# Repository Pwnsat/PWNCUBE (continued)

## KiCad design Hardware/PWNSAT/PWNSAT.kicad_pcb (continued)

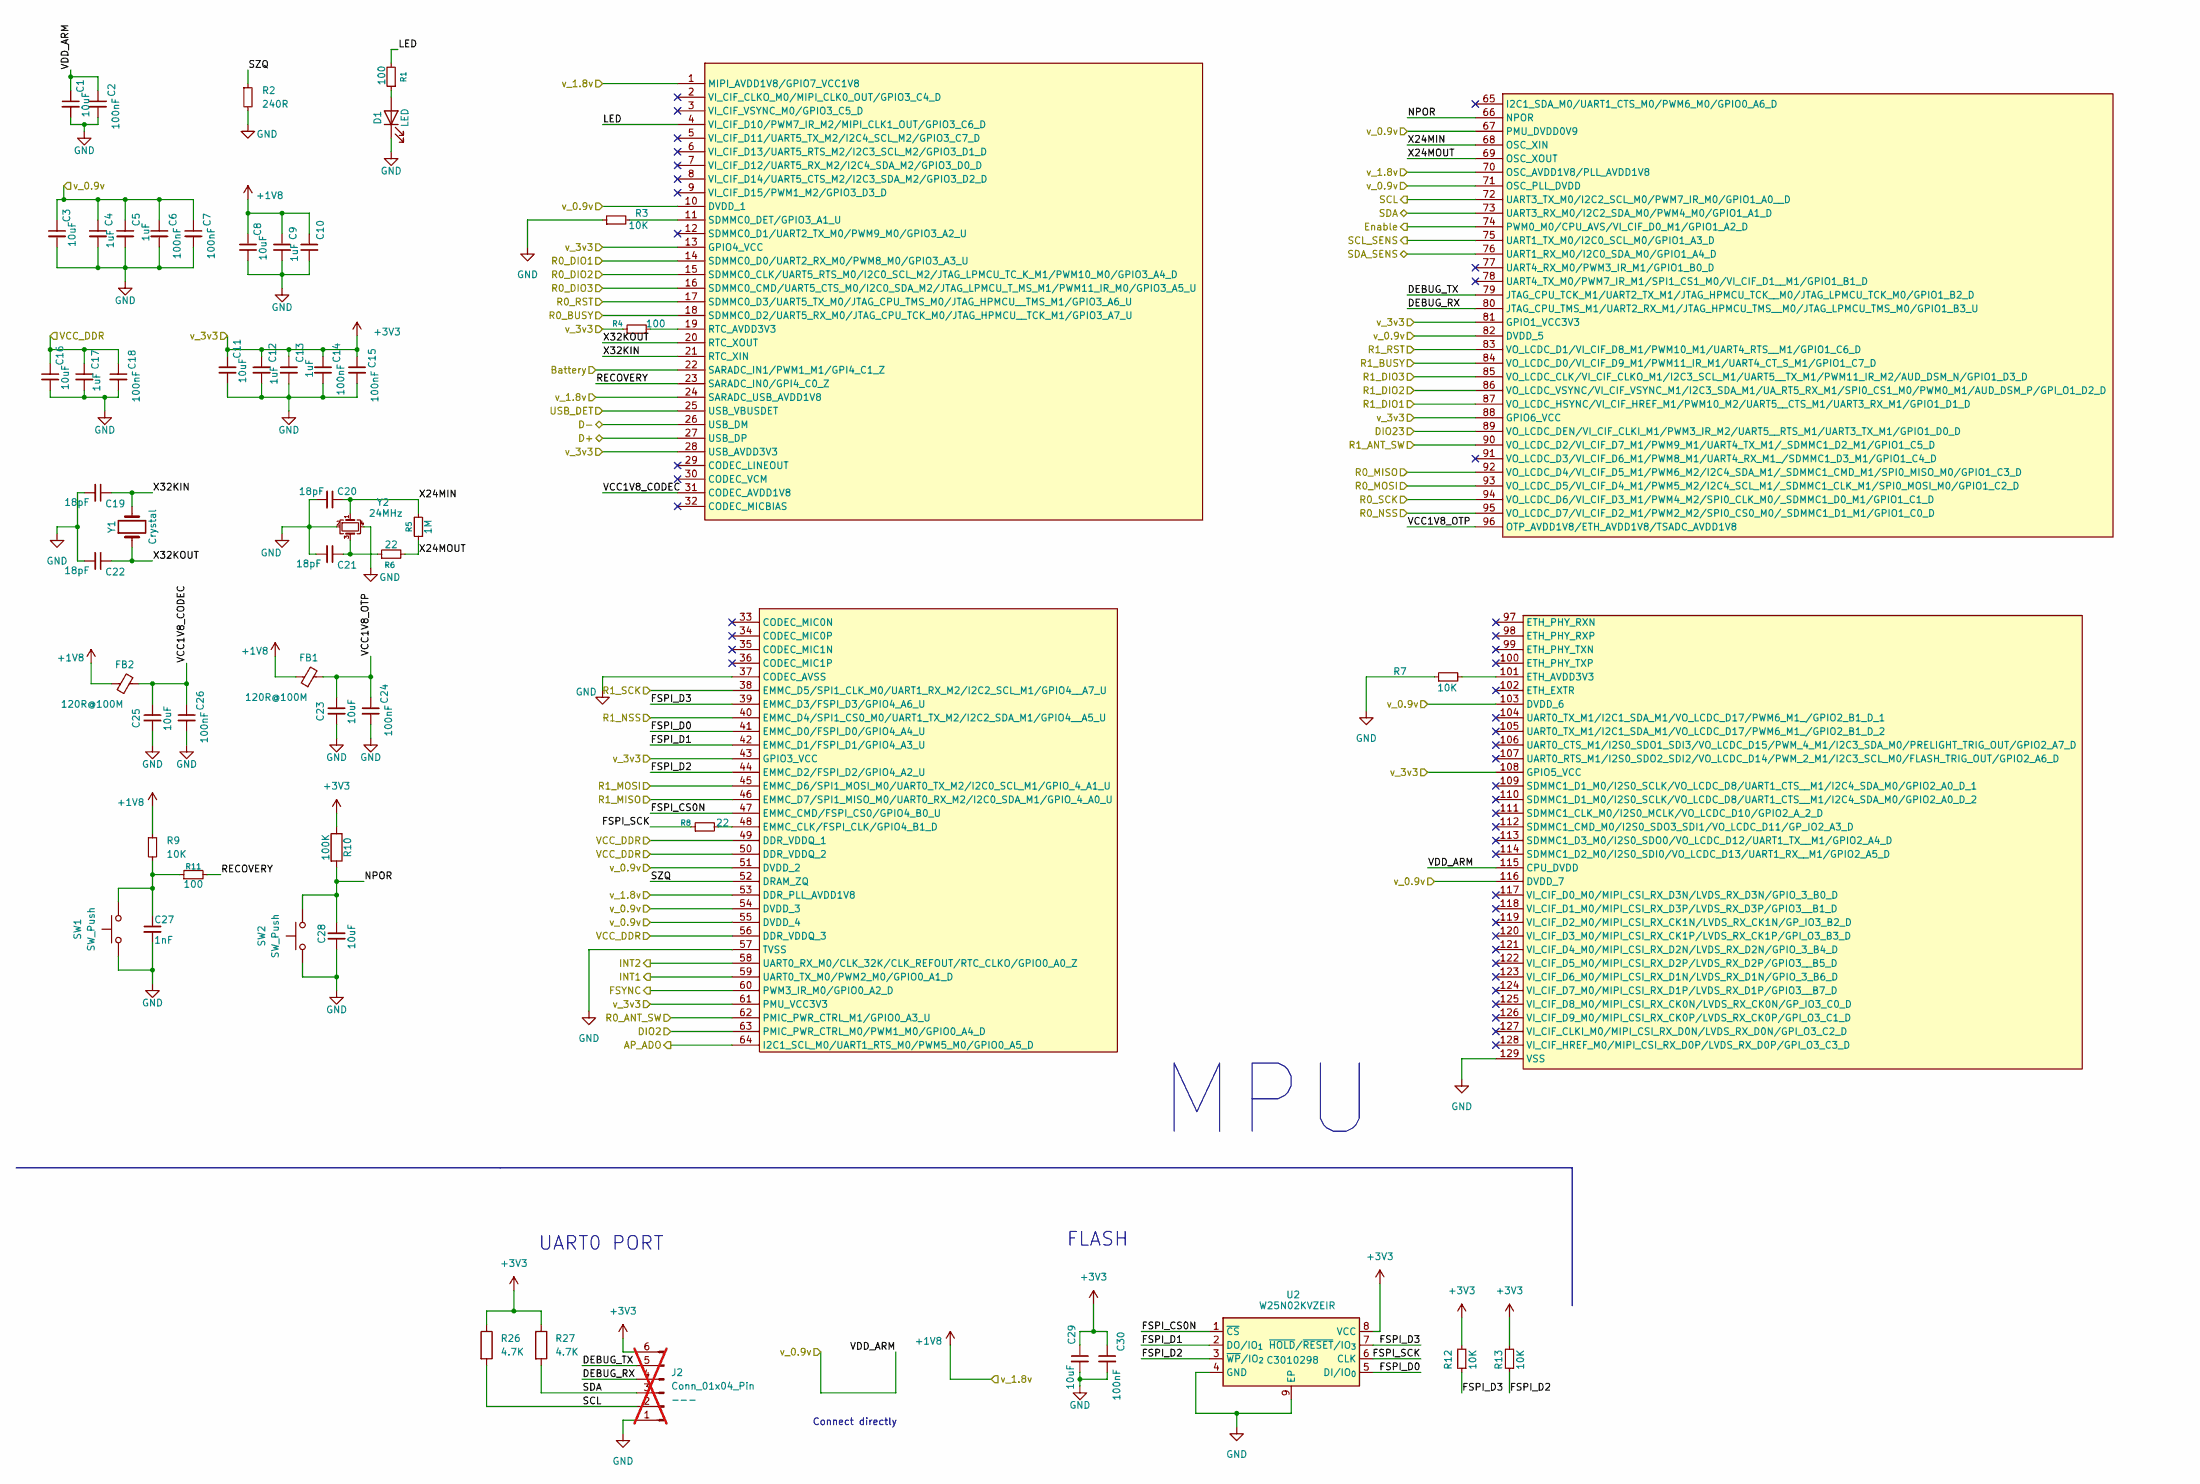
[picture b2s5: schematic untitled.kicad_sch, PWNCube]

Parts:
C1, C3, C8, C11, C16, C23, C25, C28, C29: 10uF; C_0603_1608Metric; LCSC# C96446
C2, C6, C7, C14, C15, C18, C24, C26, C30: 100nF; C_0402_1005Metric_Pad0.74x0.62mm_HandSolder; LCSC# C56392
C4, C5, C9, C10, C12, C13, C17: 1uF; C_0402_1005Metric_Pad0.74x0.62mm_HandSolder; LCSC# C52923
C19, C20, C21, C22: 18pF; C_0402_1005Metric_Pad0.74x0.62mm_HandSolder; LCSC# C161534
C27: 1nF; C_0402_1005Metric_Pad0.74x0.62mm_HandSolder; LCSC# C189467
D1: LED; LED_0603_1608Metric; LCSC# C375573
FB1, FB2: 120R@100M; L_0603_1608Metric; LCSC# C14709
J2: Conn_01x04_Pin; PinHeader_1x06_P2.54mm_Vertical; LCSC# ---; not fitted
R1, R4, R11: 100; R_0603_1608Metric; LCSC# C253328
R2: 240R; R_0402_1005Metric_Pad0.72x0.64mm_HandSolder; LCSC# C728568
R3, R7, R9, R12, R13: 10K; R_0402_1005Metric_Pad0.72x0.64mm_HandSolder; LCSC# C2759535
R5: 1M; R_0402_1005Metric_Pad0.72x0.64mm_HandSolder; LCSC# C131492
R6, R8: 22; R_0603_1608Metric; LCSC# C313374
R10: 100K; R_0402_1005Metric_Pad0.72x0.64mm_HandSolder; LCSC# C844674
R26, R27: 4.7K; R_0402_1005Metric_Pad0.72x0.64mm_HandSolder; LCSC# C400631
SW1, SW2: SW_Push; TS1088R02026; LCSC# C455281
U1: RV1106G3; LCSC# C5328706
U2: W25N02KVZEIR; WSON-8-1EP_8x6mm_P1.27mm_EP3.4x4.3mm; LCSC# C3010298
Y1: Crystal; Crystal_SMD_3215-2Pin_3.2x1.5mm; LCSC# C620155
Y2: 24MHz; Crystal_SMD_3225-4Pin_3.2x2.5mm; LCSC# C70590

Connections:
+1V8: C8.1, C9.1, C10.1, FB1.1, FB2.1, R9.1, U1.1 (MIPI_AVDD1V8/GPIO7_VCC1V8), U1.24 (SARADC_USB_AVDD1V8), U1.53 (DDR_PLL_AVDD1V8), U1.70 (OSC_AVDD1V8/PLL_AVDD1V8); also elsewhere on the board
+3V3: C11.1, C12.1, C13.1, C14.1, C15.1, C29.1, C30.1, J2.6, R4.1, R10.1, R12.2, R13.2, R26.1, R27.1, U1.13 (GPIO4_VCC), U1.28 (USB_AVDD3V3), U1.43 (GPIO3_VCC), U1.61 (PMU_VCC3V3), U1.81 (GPIO1_VCC3V3), U1.88 (GPIO6_VCC), U1.108 (GPIO5_VCC), U2.8 (VCC); also elsewhere on the board
/Sensor/AP_ADO: U1.64 (I2C1_SCL_M0/UART1_RTS_M0/PWM5_M0/GPIO0_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); also elsewhere on the board
/Sensor/DIO2: U1.63 (PMIC_PWR_CTRL_M0/PWM1_M0/GPIO0_A4_D); also elsewhere on the board
/Sensor/DIO23: U1.89 (VO_LCDC_DEN/VI_CIF_CLKI_M1/PWM3_IR_M2/U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); also elsewhere on the board
/Sensor/FSYNC: U1.60 (PWM3_IR_M0/GPIO0_A2_D); also elsewhere on the board
/Sensor/INT1: U1.59 (UART0_TX_M0/PWM2_M0/GPIO0_A1_D); also elsewhere on the board
/Sensor/INT2: U1.58 (UART0_RX_M0/CLK_32K/CLK_REFOUT/RTC_CLKO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); also elsewhere on the board
/Sensor/R0_ANT_SW: U1.62 (PMIC_PWR_CTRL_M1/GPIO0_A3_U); also elsewhere on the board
/Sensor/R0_BUSY: U1.18 (SDMMC0_D2/UART5_RX_M0/JTAG_CPU_TCK_M0/J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); also elsewhere on the board
/Sensor/R0_DIO1: U1.14 (SDMMC0_D0/UART2_RX_M0/PWM8_M0/GPIO3_A3_U); also elsewhere on the board
/Sensor/R0_DIO2: U1.15 (SDMMC0_CLK/UART5_RTS_M0/I2C0_SCL_M2/JTA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); also elsewhere on the board
/Sensor/R0_DIO3: U1.16 (SDMMC0_CMD/UART5_CTS_M0/I2C0_SDA_M2/JTA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); also elsewhere on the board
/Sensor/R0_MISO: U1.92 (VO_LCDC_D4/VI_CIF_D5_M1/PWM6_M2/I2C4_SD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); also elsewhere on the board
/Sensor/R0_MOSI: U1.93 (VO_LCDC_D5/VI_CIF_D4_M1/PWM5_M2/I2C4_SC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); also elsewhere on the board
/Sensor/R0_NSS: U1.95 (VO_LCDC_D7/VI_CIF_D2_M1/PWM2_M2/SPI0_CS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); also elsewhere on the board
/Sensor/R0_RST: U1.17 (SDMMC0_D3/UART5_TX_M0/JTAG_CPU_TMS_M0/J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); also elsewhere on the board
/Sensor/R0_SCK: U1.94 (VO_LCDC_D6/VI_CIF_D3_M1/PWM4_M2/SPI0_CL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); also elsewhere on the board
/Sensor/R1_ANT_SW: U1.90 (VO_LCDC_D2/VI_CIF_D7_M1/PWM9_M1/UART4_T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); also elsewhere on the board
/Sensor/R1_BUSY: U1.84 (VO_LCDC_D0/VI_CIF_D9_M1/PWM11_IR_M1/UAR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); also elsewhere on the board
/Sensor/R1_DIO1: U1.87 (VO_LCDC_HSYNC/VI_CIF_HREF_M1/PWM10_M2/U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); also elsewhere on the board
/Sensor/R1_DIO2: U1.86 (VO_LCDC_VSYNC/VI_CIF_VSYNC_M1/I2C3_SDA_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); also elsewhere on the board
/Sensor/R1_DIO3: U1.85 (VO_LCDC_CLK/VI_CIF_CLKO_M1/I2C3_SCL_M1/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); also elsewhere on the board
/Sensor/R1_MISO: U1.46 (EMMC_D7/SPI1_MISO_M0/UART0_RX_M2/I2C0_S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); also elsewhere on the board
/Sensor/R1_MOSI: U1.45 (EMMC_D6/SPI1_MOSI_M0/UART0_TX_M2/I2C0_S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); also elsewhere on the board
/Sensor/R1_NSS: U1.40 (EMMC_D4/SPI1_CS0_M0/UART1_TX_M2/I2C2_SD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); also elsewhere on the board
/Sensor/R1_RST: U1.83 (VO_LCDC_D1/VI_CIF_D8_M1/PWM10_M1/UART4_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); also elsewhere on the board
/Sensor/R1_SCK: U1.38 (EMMC_D5/SPI1_CLK_M0/UART1_RX_M2/I2C2_SC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); also elsewhere on the board
/Sensor/SCL_SENS: U1.75 (UART1_TX_M0/I2C0_SCL_M0/GPIO1_A3_D); also elsewhere on the board
/Sensor/SDA_SENS: U1.76 (UART1_RX_M0/I2C0_SDA_M0/GPIO1_A4_D); also elsewhere on the board
/Source_Connector/Battery: U1.22 (SARADC_IN1/PWM1_M1/GPI4_C1_Z); also elsewhere on the board
/Source_Connector/Enable: U1.74 (PWM0_M0/CPU_AVS/VI_CIF_D0_M1/GPIO1_A2_D); also elsewhere on the board
/Source_Connector/USB_DET: U1.25 (USB_VBUSDET); also elsewhere on the board
/USB_Selector/D+: U1.27 (USB_DP); also elsewhere on the board
/USB_Selector/D-: U1.26 (USB_DM); also elsewhere on the board
/core/DEBUG_RX: J2.4, U1.80 (JTAG_CPU_TMS_M1/UART2_RX_M1/JTAG_HPMCU_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)
/core/DEBUG_TX: J2.5, U1.79 (JTAG_CPU_TCK_M1/UART2_TX_M1/JTAG_HPMCU_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)
/core/FSPI_CS0N: U1.47 (EMMC_CMD/FSPI_CS0/GPIO4_B0_U), U2.1 (~CS)
/core/FSPI_D0: U1.41 (EMMC_D0/FSPI_D0/GPIO4_A4_U), U2.5 (DI/IO_{0})
/core/FSPI_D1: U1.42 (EMMC_D1/FSPI_D1/GPIO4_A3_U), U2.2 (DO/IO_{1})
/core/FSPI_D2: R13.1, U1.44 (EMMC_D2/FSPI_D2/GPIO4_A2_U), U2.3 (~WP/IO_{2})
/core/FSPI_D3: R12.1, U1.39 (EMMC_D3/FSPI_D3/GPIO4_A6_U), U2.7 (~HOLD/~RESET/IO_{3})
/core/FSPI_SCK: R8.1, U2.6 (CLK)
/core/LED: R1.2, U1.4 (VI_CIF_D10/PWM7_IR_M2/MIPI_CLK1_OUT/GPI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)
/core/NPOR: C28.1, R10.2, SW2.2, U1.66 (NPOR)
/core/RECOVERY: R11.2, U1.23 (SARADC_IN0/GPI4_C0_Z)
/core/SCL: J2.2, R26.2, U1.72 (UART3_TX_M0/I2C2_SCL_M0/PWM7_IR_M0/GPIO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)
/core/SDA: J2.3, R27.2, U1.73 (UART3_RX_M0/I2C2_SDA_M0/PWM4_M0/GPIO1_A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)
/core/SZQ: R2.1, U1.52 (DRAM_ZQ)
/core/VCC1V8_CODEC: C25.1, C26.1, FB2.2, U1.31 (CODEC_AVDD1V8)
/core/VCC1V8_OTP: C23.1, C24.1, FB1.2, U1.96 (OTP_AVDD1V8/ETH_AVDD1V8/TSADC_AVDD1V8)
/core/VCC_DDR: C16.1, C17.1, C18.1, U1.49 (DDR_VDDQ_1), U1.50 (DDR_VDDQ_2), U1.56 (DDR_VDDQ_3); also elsewhere on the board
/core/VDD_ARM: C1.1, C2.1, C3.1, C4.1, C5.1, C6.1, C7.1, U1.10 (DVDD_1), U1.51 (DVDD_2), U1.54 (DVDD_3), U1.55 (DVDD_4), U1.67 (PMU_DVDD0V9), U1.71 (OSC_PLL_DVDD), U1.82 (DVDD_5), U1.103 (DVDD_6), U1.115 (CPU_DVDD), U1.116 (DVDD_7); also elsewhere on the board
/core/X24MIN: C20.1, R5.1, U1.68 (OSC_XIN), Y2.1
/core/X24MOUT: R5.2, R6.2, U1.69 (OSC_XOUT)
/core/X32KIN: C19.1, U1.21 (RTC_XIN), Y1.2
/core/X32KOUT: C22.1, U1.20 (RTC_XOUT), Y1.1
GND: C1.2, C2.2, C3.2, C4.2, C5.2, C6.2, C7.2, C8.2, C9.2, C10.2, C11.2, C12.2, C13.2, C14.2, C15.2, C16.2, C17.2, C18.2, C19.2, C20.2, C21.2, C22.2, C23.2, C24.2, C25.2, C26.2, C27.2, C28.2, C29.2, C30.2, D1.1 (K), J2.1, R2.2, R3.1, R7.1, SW1.1, SW2.1, U1.37 (CODEC_AVSS), U1.57 (TVSS), U1.129 (VSS), U2.4 (GND), U2.9 (EP), Y2.2, Y2.4; also elsewhere on the board
unnamed: C21.1, R6.1, Y2.3
unnamed: C27.1, R9.2, R11.1, SW1.2
unnamed: D1.2 (A), R1.1
unnamed: R4.2, U1.19 (RTC_AVDD3V3)
unnamed: R3.2, U1.11 (SDMMC0_DET/GPIO3_A1_U)
unnamed: R8.2, U1.48 (EMMC_CLK/FSPI_CLK/GPIO4_B1_D)
unnamed: R7.2, U1.101 (ETH_AVDD3V3)

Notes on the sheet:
FLASH
UART0 PORT
MPU
Connect directly

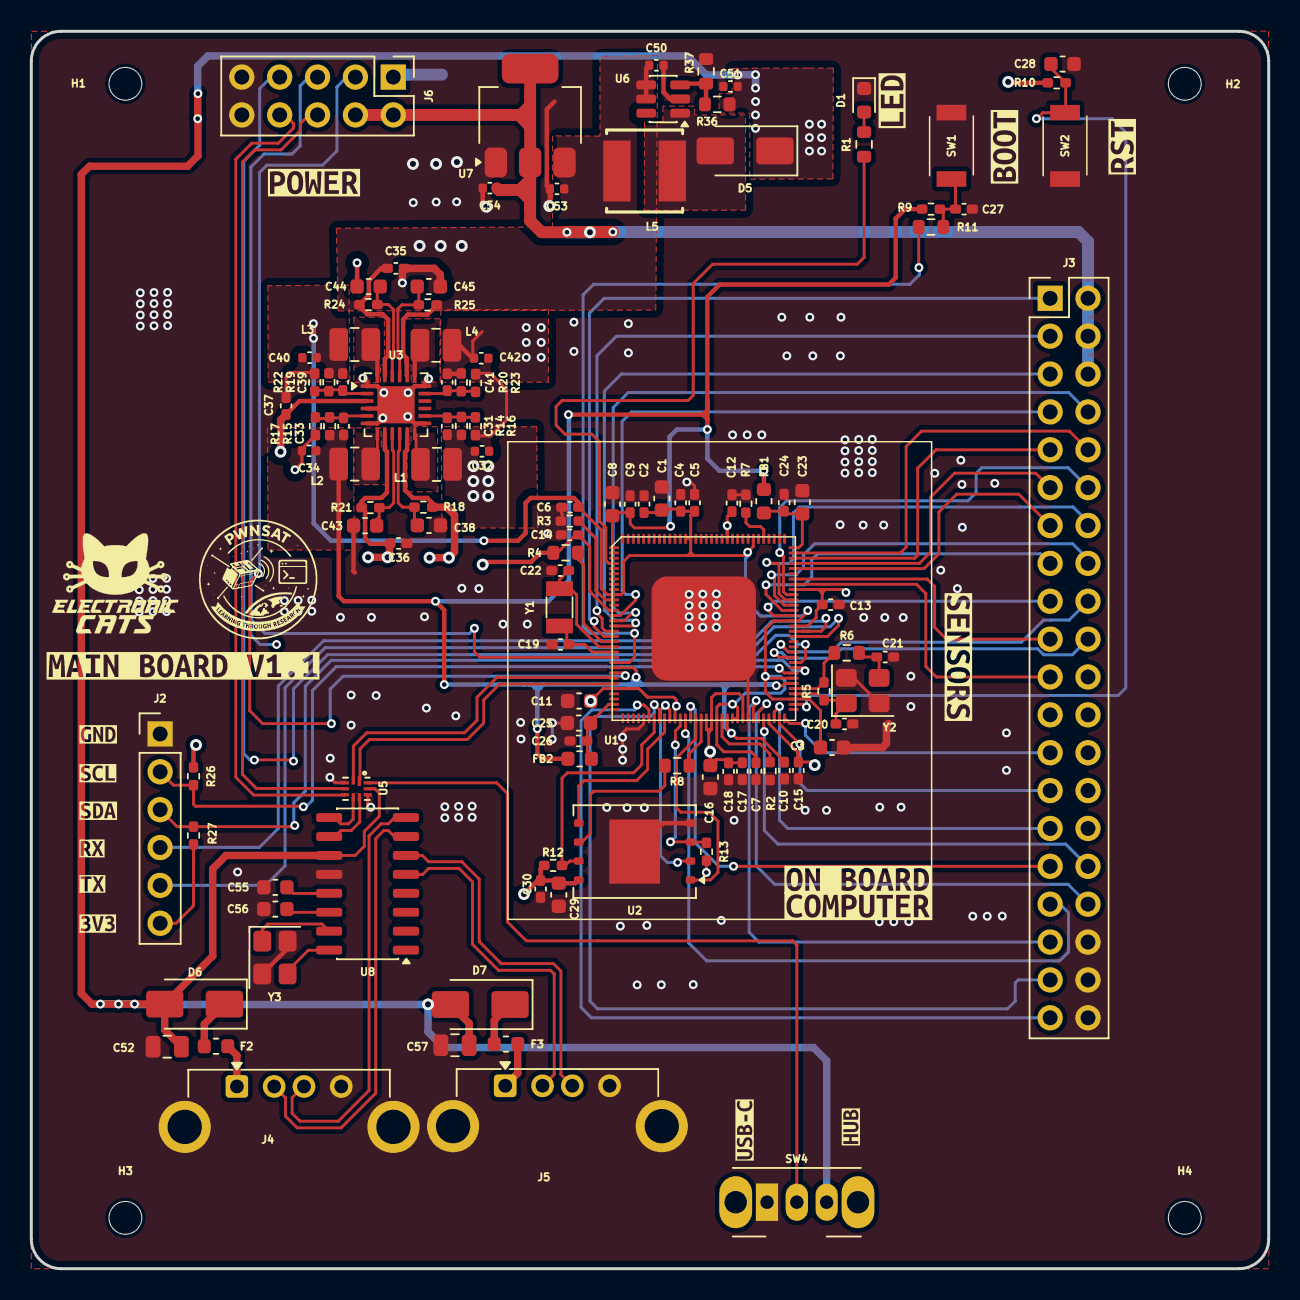
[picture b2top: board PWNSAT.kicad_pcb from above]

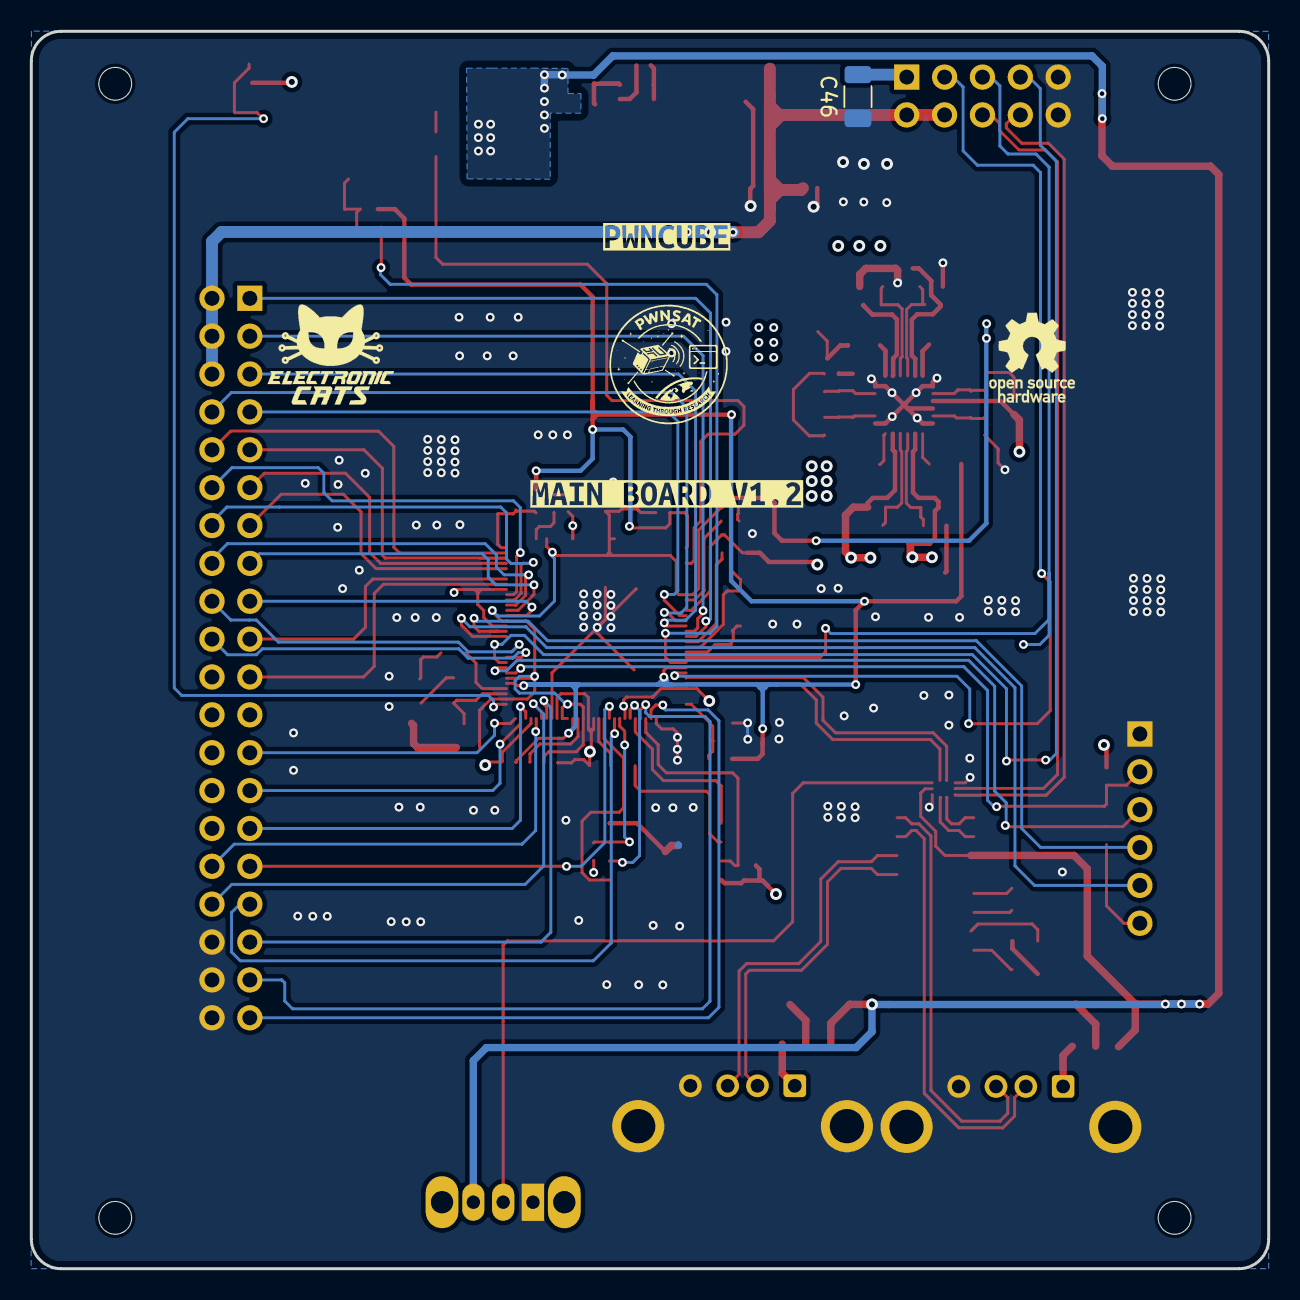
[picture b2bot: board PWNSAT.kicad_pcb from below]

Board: 4 copper layers, 83.0 x 83.0 mm, 136 parts (3 on the bottom side), 99 nets.

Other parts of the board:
H1, H2, H3, H4: MountingHole; MountingHole_2.2mm_M2
kibuzzard-69B43A9C: G***; kibuzzard-69B43A9C
kibuzzard-69B883B0: G***; kibuzzard-69B883B0
kibuzzard-6989FAE0: G***; kibuzzard-6989FAE0
kibuzzard-6989FAEE: G***; kibuzzard-6989FAEE
kibuzzard-698516AC: G***; kibuzzard-698516AC
kibuzzard-698516D4: G***; kibuzzard-698516D4
kibuzzard-698516F5: G***; kibuzzard-698516F5
kibuzzard-698517BF: G***; kibuzzard-698517BF
kibuzzard-698517CD: G***; kibuzzard-698517CD
kibuzzard-698517E4: G***; kibuzzard-698517E4
kibuzzard-698517F0: G***; kibuzzard-698517F0
kibuzzard-698615E5: G***; kibuzzard-698615E5
kibuzzard-6985157B: G***; kibuzzard-6985157B
kibuzzard-6985168F: G***; kibuzzard-6985168F
kibuzzard-6986164F: G***; kibuzzard-6986164F
kibuzzard-69851805: G***; kibuzzard-69851805
kibuzzard-69851812: G***; kibuzzard-69851812
kibuzzard-69861606: G***; kibuzzard-69861606

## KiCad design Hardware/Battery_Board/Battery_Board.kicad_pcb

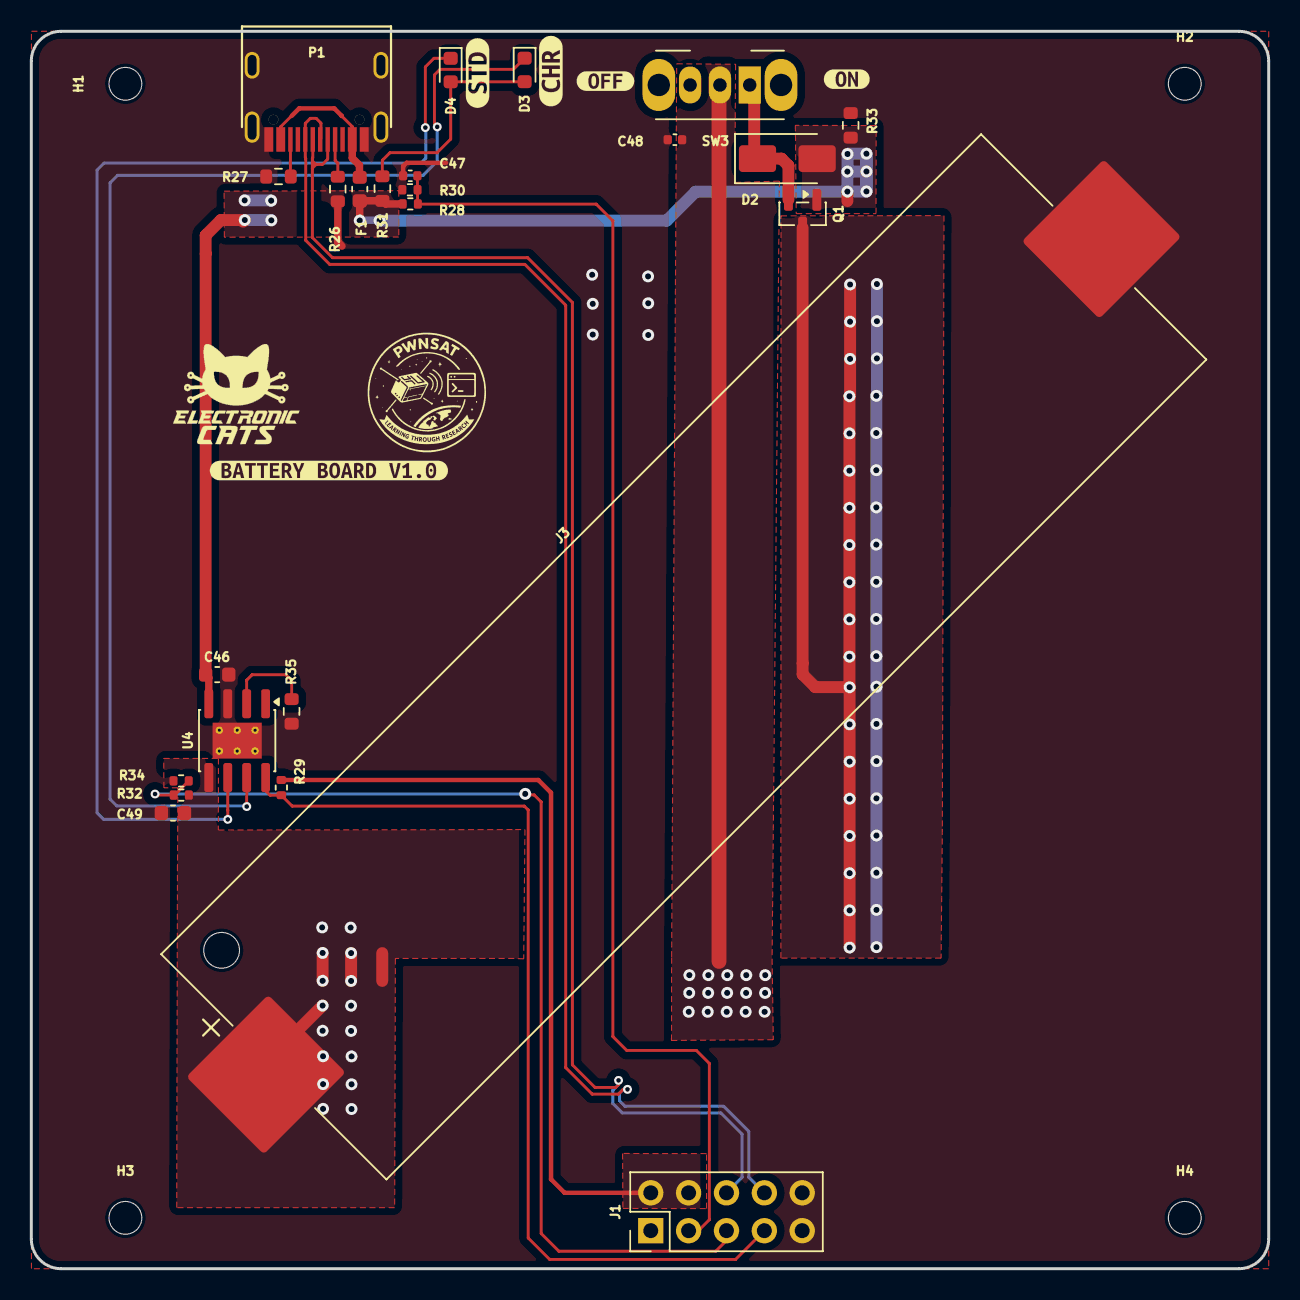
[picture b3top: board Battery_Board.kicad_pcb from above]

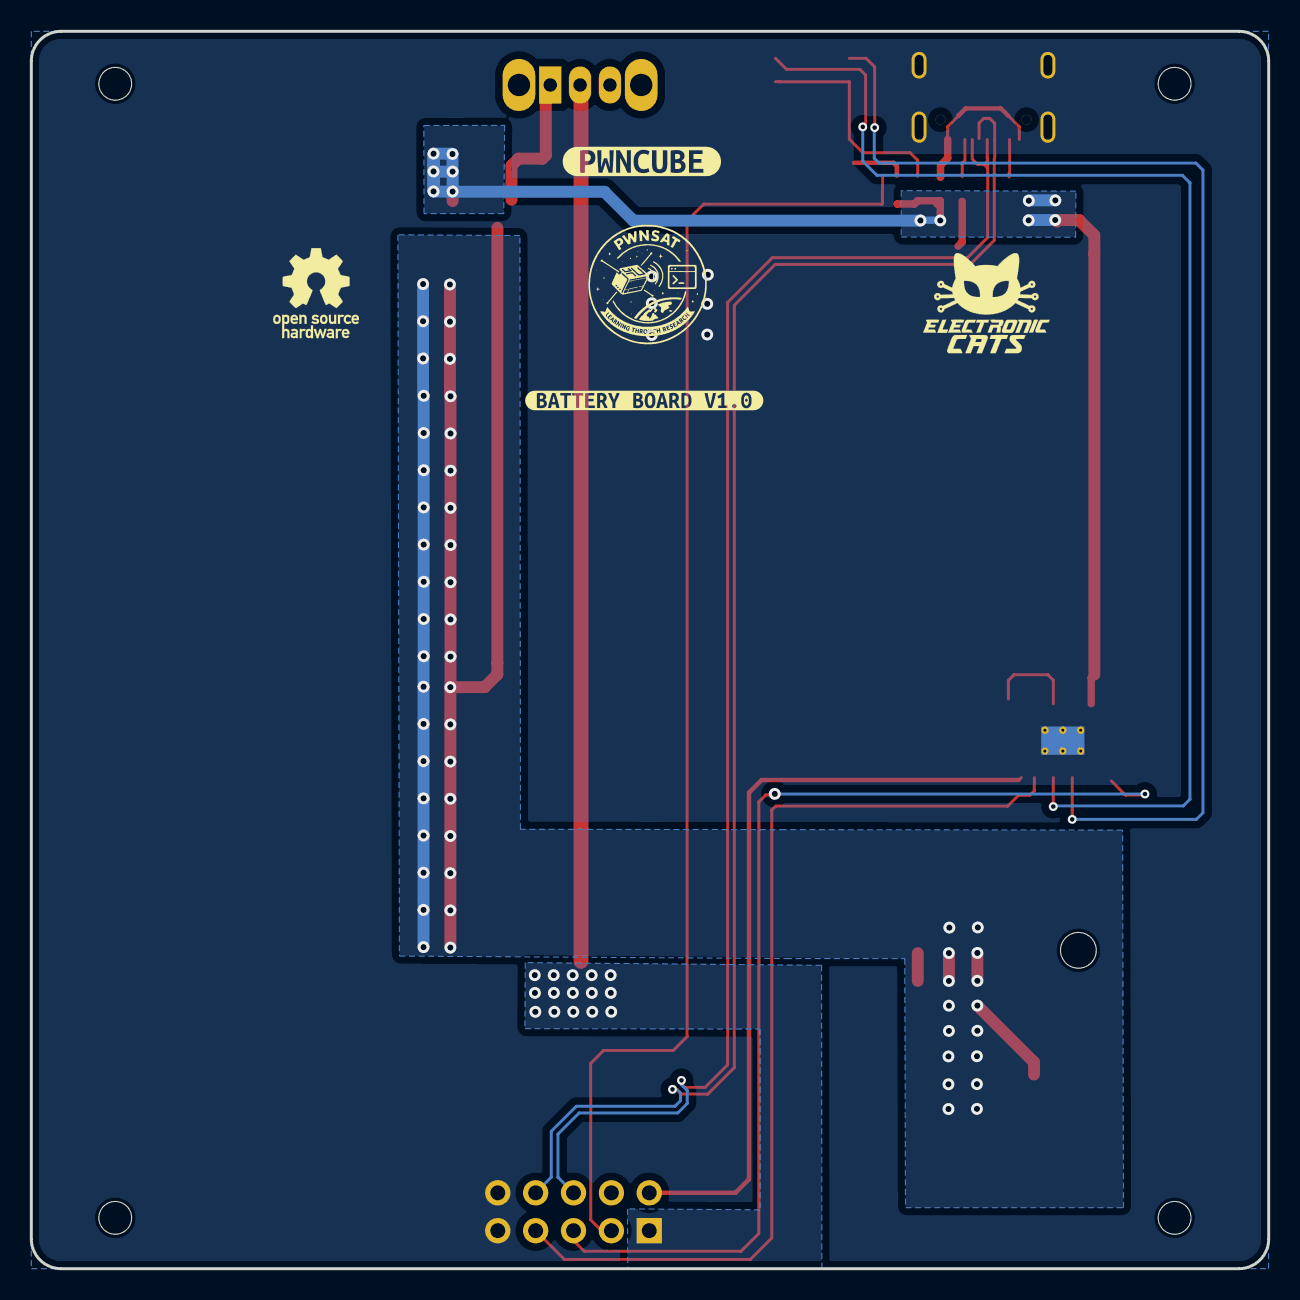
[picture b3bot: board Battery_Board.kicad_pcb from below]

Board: 2 copper layers, 83.0 x 83.0 mm, 35 parts (2 on the bottom side), 18 nets.

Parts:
C46, C49: 10uF; C_0603_1608Metric
C47: 100nF; C_0402_1005Metric
C48: 10uF; C_0402_1005Metric
D2: SS34; D_SMA
D3, D4: LED; LED_0603_1608Metric
F1: 2A; Fuse_0603_1608Metric
H1, H2, H3, H4: MountingHole; MountingHole_2.2mm_M2
J1: Source; PinHeader_2x05_P2.54mm_Vertical
J3: Battery; BatteryHolder_Keystone_1042_1x18650
P1: USB_C_Plug_USB2.0; C393939
Q1: DMG3415U-7; SOT-23
R26, R27: 5k1; R_0603_1608Metric
R28, R29, R34: 10K; R_0402_1005Metric
R30: 18k; R_0402_1005Metric
R31, R35: 2K; R_0603_1608Metric
R32: 10.7K; R_0402_1005Metric
R33: 100K; R_0603_1608Metric
SW3: ON; SW_Slide_SPDT_Angled_CK_OS102011MA1Q
U4: TP4056; SOIC-8-1EP_3.9x4.9mm_P1.27mm_EP2.41x3.3mm_ThermalVias
kibuzzard-698511AF: G***; kibuzzard-698511AF
kibuzzard-698511C2: G***; kibuzzard-698511C2
kibuzzard-6985125C: G***; kibuzzard-6985125C
kibuzzard-69851248, kibuzzard-69851248#2: G***; kibuzzard-69851248
kibuzzard-69851454: G***; kibuzzard-69851454
kibuzzard-69851473: G***; kibuzzard-69851473

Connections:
+3.3V: J1.2, J1.4, R29.1
+BATT: C49.1, J3.1, Q1.3 (D), R32.1, U4.5 (BAT)
/Batt_Connector/2_DN: J1.6, P1.A7 (D-)
/Batt_Connector/2_DP: J1.8, P1.A6 (D+)
/Batt_Connector/Battery: J1.5, R32.2, R34.1
/Batt_Connector/Enable: J1.7, R29.2, U4.8 (CE)
/Batt_Connector/USB_DET: C47.1, J1.3, R28.1, R30.1
GND: C46.1, C47.2, C48.2, C49.2, J1.9, J1.10, J3.2, P1.A1 (GND), P1.S1 (SHIELD), R26.1, R27.1, R30.2, R33.2, R34.2, R35.2, U4.3 (GND), U4.9 (EPAD)
unnamed: D2.1 (K), Q1.2 (S), SW3.1 (A)
unnamed: D3.2 (A), D4.2 (A), R31.2
unnamed: D3.1 (K), U4.7 (~CHRG)
unnamed: D4.1 (K), U4.6 (~STDBY)
unnamed: F1.1, P1.A4 (VBUS)
unnamed: P1.A5 (CC), R26.2
unnamed: P1.B5 (VCONN), R27.2
unnamed: R35.1, U4.2 (PROG)
VBUS: C46.2, D2.2 (A), F1.2, Q1.1 (G), R28.2, R31.1, R33.1, U4.4 (V_{CC})
VCC: C48.1, J1.1, SW3.2 (B)

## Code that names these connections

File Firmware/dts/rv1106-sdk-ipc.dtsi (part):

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	/*
	 * ICM-42670-P 6-axis IMU, same I2C0 bus (AP_SCKL=GPIO1_A3,
	 * AP_SDI=GPIO1_A4). AP_AD0=GPIO0_A5 is forced low by a gpio-hog
	 * (see &gpio0 below) so the address is 0x68. INT1=GPIO0_A1 is wired
	 * as the data-ready interrupt; INT2=GPIO0_A0 and FSYNC=GPIO0_A2 are
	 * routed for future use.
	 */
	icm42670: icm42670@68 {
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	};

	icm42670 {
		/* INT1, INT2, FSYNC and AP_AD0 as GPIO (i2c SCL/SDA via i2c0m0). */
		icm42670_pins: icm42670-pins {
			rockchip,pins =
				<0 RK_PA1 RK_FUNC_GPIO &pcfg_pull_none>,
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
